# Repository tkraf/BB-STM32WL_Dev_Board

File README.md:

# BB-STM32WL_Dev_Board

A development board for the BB-STM32WL that supports LiPo batteries, solar charging, USB programming, and a virtual COM port.

## Features

- **LiPo Battery Support**: Easily connect and use LiPo batteries for power.
- **Solar Charging**: Integrated solar charging capabilities to keep your board powered sustainably.
- **USB Programming**: Convenient USB interface for programming the device.
- **Virtual COM Port**: Access a virtual COM port for serial communication.

### Setup

1. **Powering the Board**:
    - Connect a LiPo battery to the BAT connector on the back of the board.
    - Optionally, connect a solar panel to the VIN connector.
    - The board can also be powered through the USB port.

2. **Programming**:
    - Connect the board to your computer using a USB cable.
    - The board should be recognized as a USB Serial device.
    - Use your preferred development environment to program the board.

3. **Using the Virtual COM Port**:
    - Once connected via USB, the board will provide a virtual COM port.
    - Use any serial communication software to interact with the board.

## License

This project is licensed under the MIT License. See the [LICENSE](https://github.com/tkraf/BB-STM32WL_Dev_Board/blob/main/LICENSE) file for details.

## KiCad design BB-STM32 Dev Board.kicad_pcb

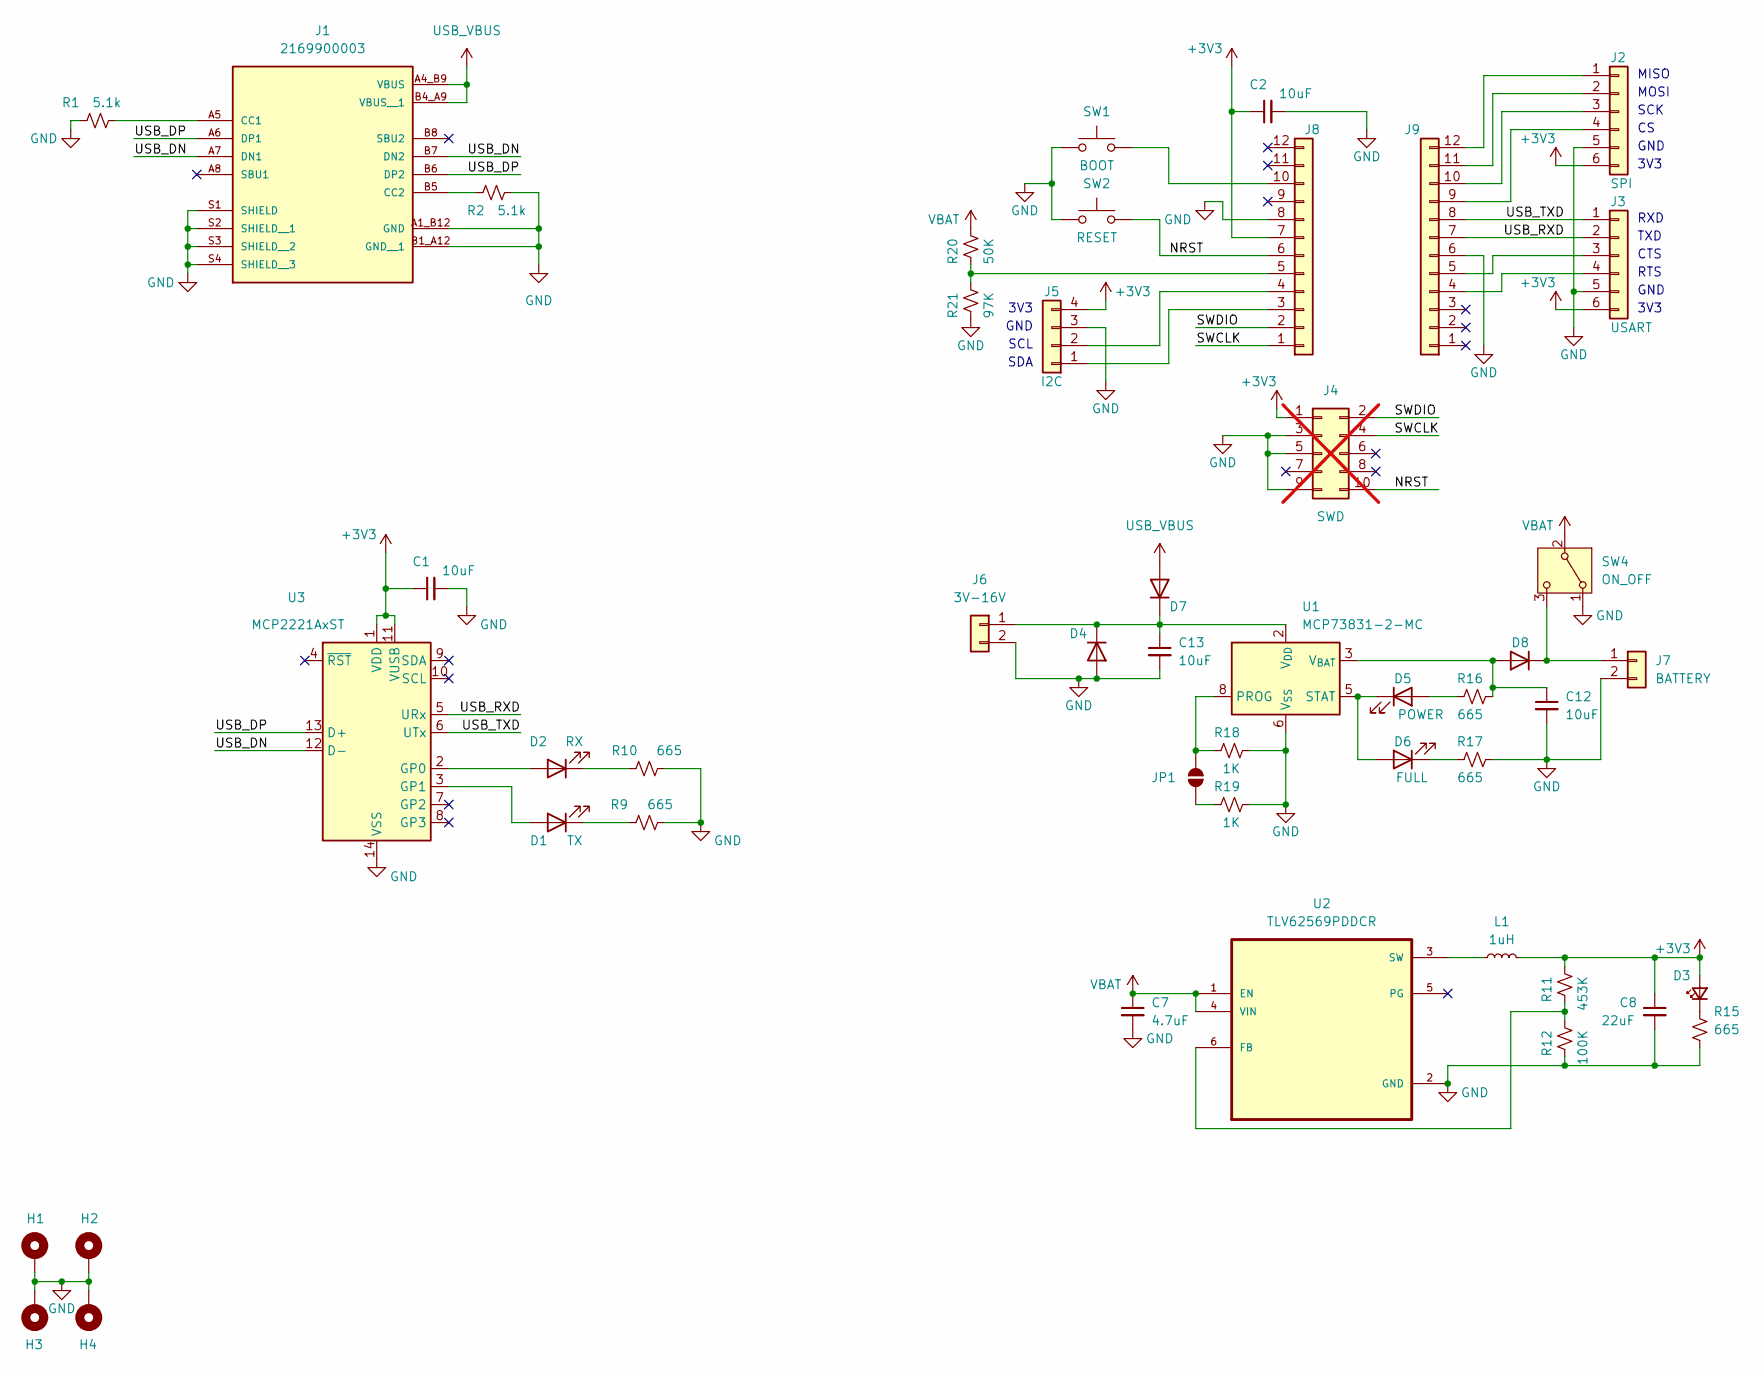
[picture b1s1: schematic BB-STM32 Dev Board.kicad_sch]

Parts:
C1, C2, C12, C13: 10uF; C_0805_2012Metric_Pad1.18x1.45mm_HandSolder; Manufacturer_Part_Number CL21A106KOQNNNE
C7: 4.7uF; C_0402_1005Metric_Pad0.74x0.62mm_HandSolder; Manufacturer_Part_Number CL05A475MP5NRNC
C8: 22uF; C_0805_2012Metric_Pad1.18x1.45mm_HandSolder; Manufacturer_Part_Number CL21A226MAYNNNE
D1: TX; LED_0402_1005Metric_Pad0.77x0.64mm_HandSolder; Manufacturer_Part_Number B1811URO-20D000113U1930
D2: RX; LED_0402_1005Metric_Pad0.77x0.64mm_HandSolder; Manufacturer_Part_Number B1811URO-20D000113U1930
D3: LED_Small; LED_0402_1005Metric_Pad0.77x0.64mm_HandSolder; Manufacturer_Part_Number B1811URO-20D000113U1930
D4, D7, D8: D_SOD-123; Manufacturer_Part_Number SBA140AS_R1_00001
D5: POWER; LED_0402_1005Metric_Pad0.77x0.64mm_HandSolder; Manufacturer_Part_Number B1811URO-20D000113U1930
D6: FULL; LED_0402_1005Metric_Pad0.77x0.64mm_HandSolder; Manufacturer_Part_Number B1811URO-20D000113U1930
H1, H2, H3, H4: MountingHole_Pad; MountingHole_3.2mm_M3_Pad_TopBottom
J1: 2169900003; MOLEX_2169900003; PARTREV A1
J2: SPI; PinSocket_1x06_P2.54mm_Vertical; Manufacturer_Part_Number 61300611821
J3: USART; PinSocket_1x06_P2.54mm_Vertical; Manufacturer_Part_Number 61300611821
J4: SWD; not fitted
J5: I2C; PinSocket_1x04_P2.54mm_Vertical; Manufacturer_Part_Number 61300411821
J6: 3V-16V; Molex_PicoBlade_53261-0271_1x02-1MP_P1.25mm_Horizontal; Manufacturer_Part_Number 0532610271
J7: BATTERY; Molex_PicoBlade_53261-0271_1x02-1MP_P1.25mm_Horizontal; Manufacturer_Part_Number 0532610271
J8, J9: Conn_01x12; PinSocket_1x12_P2.54mm_Vertical
JP1: SolderJumper_2_Open; SolderJumper-2_P1.3mm_Open_RoundedPad1.0x1.5mm
L1: 1uH; Bourns SRP4020TA; Manufacturer_Part_Number XFL4020-102MEB
R1, R2: 5.1k; R_0402_1005Metric_Pad0.72x0.64mm_HandSolder; Manufacturer_Part_Number RC0402FR-075K1L
R9, R10, R15, R16, R17: 665; R_0402_1005Metric_Pad0.72x0.64mm_HandSolder; Manufacturer_Part_Number ERJ-2RKF6650X
R11: 453K; R_0402_1005Metric_Pad0.72x0.64mm_HandSolder; Manufacturer_Part_Number CRCW0402453KFKED
R12: 100K; R_0402_1005Metric_Pad0.72x0.64mm_HandSolder; Manufacturer_Part_Number CRCW0402100KFKED
R18, R19: 1K; R_0402_1005Metric_Pad0.72x0.64mm_HandSolder; Manufacturer_Part_Number RC0402JR-071KL
R20: 50K; R_0402_1005Metric_Pad0.72x0.64mm_HandSolder; Manufacturer_Part_Number RNCF0402DKE50K0
R21: 97K; R_0402_1005Metric_Pad0.72x0.64mm_HandSolder; Manufacturer_Part_Number RC0402FR-0797K6L
SW1: BOOT; SW_Push_1P1T_NO_6x6mm_H9.5mm
SW2: RESET; SW_Push_1P1T_NO_6x6mm_H9.5mm
SW4: ON_OFF; SW_Slide_SPDT_Angled_CK_OS102011MA1Q; Manufacturer_Part_Number SLW-864574-5A-RA-N-D
U1: MCP73831-2-MC; DFN-8-1EP_3x2mm_P0.5mm_EP1.7x1.4mm; Manufacturer_Part_Number MCP73831T-2ACI/MC
U2: TLV62569PDDCR; SOT95P280X110-6N; Manufacturer_Part_Number TLV62569PDDCR
U3: MCP2221AxST; TSSOP-14_4.4x5mm_P0.65mm

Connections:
+3V3: C1.1, C2.1, C8.1, D3.2 (A), J2.6, J3.6, J4.1, J5.4, J8.7, L1.2, R11.2, U3.1 (VDD), U3.11 (VUSB)
/NRST: J4.10, J8.6, SW2.2
/SWCLK: J4.4, J8.1
/SWDIO: J4.2, J8.2
/USB_DN: J1.A7 (DN1), J1.B7 (DN2), U3.12 (D-)
/USB_DP: J1.A6 (DP1), J1.B6 (DP2), U3.13 (D+)
/USB_RXD: J3.2, J9.7, U3.5 (URx)
/USB_TXD: J3.1, J9.8, U3.6 (UTx)
GND: C1.2, C2.2, C7.2, C8.2, C12.2, C13.2, D4.2 (A), H1.1, H2.1, H3.1, H4.1, J1.A1_B12 (GND), J1.B1_A12 (GND__1), J1.S1 (SHIELD), J1.S2 (SHIELD__1), J1.S3 (SHIELD__2), J1.S4 (SHIELD__3), J2.5, J3.5, J4.3, J4.5, J4.9, J5.3, J6.2, J7.2, J8.8, J9.6, R1.1, R2.2, R9.2, R10.1, R12.1, R15.2, R17.2, R18.2, R19.2, R21.1, SW1.1, SW2.1, SW4.1 (A), U1.6 (V_{SS}), U2.2 (GND), U3.14 (VSS)
unnamed: D1.2 (A), U3.3 (GP1)
unnamed: D1.1 (K), R9.1
unnamed: D2.2 (A), U3.2 (GP0)
unnamed: D2.1 (K), R10.2
unnamed: D3.1 (K), R15.1
unnamed: C13.1, D4.1 (K), D7.1 (K), J6.1, U1.1 (V_{DD}), U1.2 (V_{DD})
unnamed: D5.2 (A), R16.1
unnamed: D5.1 (K), D6.2 (A), U1.5 (STAT)
unnamed: D6.1 (K), R17.1
unnamed: C12.1, D8.2 (A), R16.2, U1.3 (V_{BAT}), U1.4 (V_{BAT})
unnamed: D8.1 (K), J7.1, SW4.3 (C)
unnamed: J1.A5 (CC1), R1.2
unnamed: J1.B5 (CC2), R2.1
unnamed: J2.1, J9.12
unnamed: J2.2, J9.11
unnamed: J2.3, J9.10
unnamed: J2.4, J9.9
unnamed: J3.3, J9.5
unnamed: J3.4, J9.4
unnamed: J5.1, J8.3
unnamed: J5.2, J8.4
unnamed: J8.5, R20.1, R21.2
unnamed: J8.10, SW1.2
unnamed: JP1.1 (A), R18.1, U1.8 (PROG)
unnamed: JP1.2 (B), R19.1
unnamed: R11.1, R12.2, U2.6 (FB)
unnamed: L1.1, U2.3 (SW)
USB_VBUS: D7.2 (A), J1.A4_B9 (VBUS), J1.B4_A9 (VBUS__1)
VBAT: C7.1, R20.2, SW4.2 (B), U2.1 (EN), U2.4 (VIN)

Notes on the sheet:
MISO
GND
RTS
3V3
TXD
SCL
RXD
MOSI
SDA
CTS
SCK

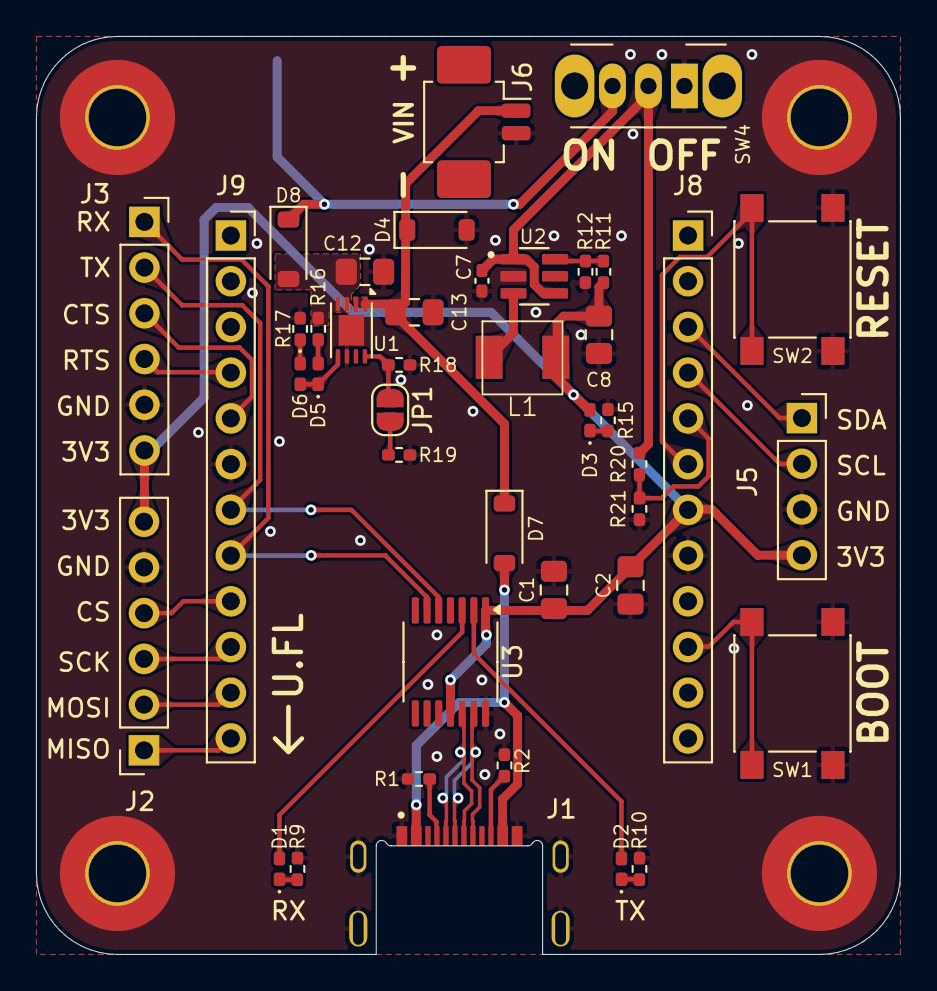
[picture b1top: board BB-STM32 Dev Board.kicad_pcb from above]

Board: 2 copper layers, 48.0 x 51.0 mm, 47 parts (1 on the bottom side), 36 nets.

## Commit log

2024-10-11 Nearly Ready Rev0
2024-10-30 Create PDF.yml
    Creates the Schematic PDF files.
2024-10-30 Update main.yml
    Adjusted Schematic PDF Actions
2024-10-30 Update main.yml
    Still trying Automatic Schematic creation
2024-10-30 Update main.yml
    More adjustments to the Schematic PDF Workflow.
2024-10-30 Update main.yml
    Changed to Kicad Actions
2024-10-31 Update main.yml
    Back to Kicad PDF
2024-10-31 Update main.yml
    Added artifacts
2024-10-31 First Run of board.
2024-10-31 Cleaned up Files
2025-01-22 Added Images and fixed USB Virtual COM Port.
2025-01-22 Added .gitignore and removed lock files.
2025-01-22 Added V2 Fab Files
